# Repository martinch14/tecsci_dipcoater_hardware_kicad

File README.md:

Diseño de Circuitos Integrados de la Carrera de Especialización en Sistemas Embebidos UBA

El siguiente diseño incluye el circuito integrado TMC5130 de la empresa TRINAMIC para el manejo de motores paso a paso
conectado con el módulo del microcontrolador ESP32D

Martin Abel Gambarotta
8vo Cohorte

Vista 3D:

Real: Fabricada y montada en Argentina Ernesto Mayer S.A. +  Asembli S.A.

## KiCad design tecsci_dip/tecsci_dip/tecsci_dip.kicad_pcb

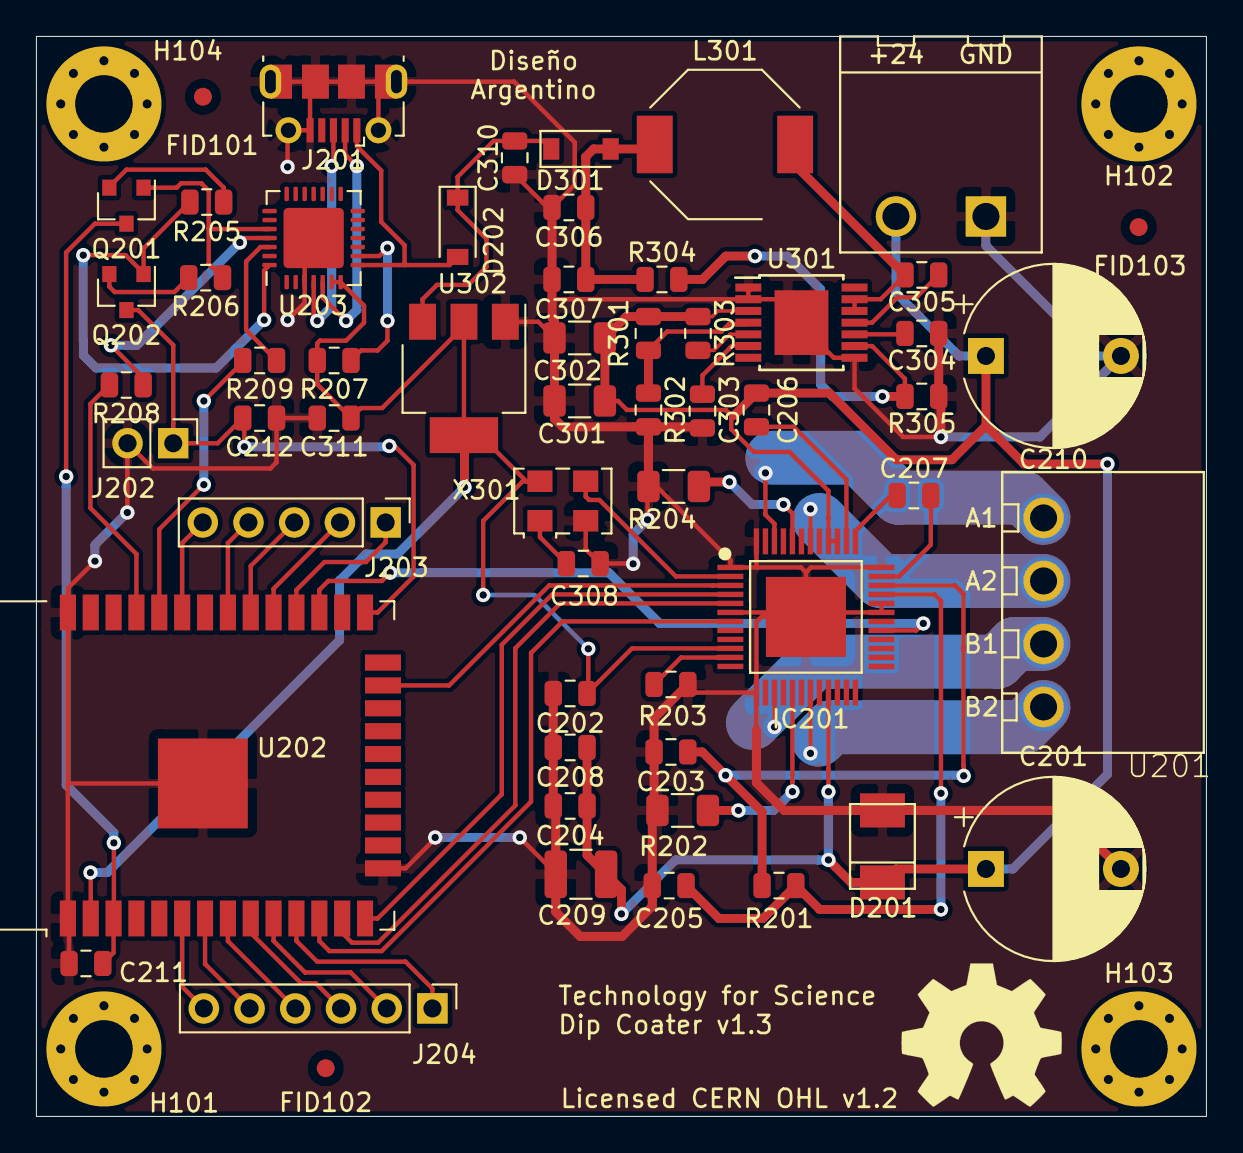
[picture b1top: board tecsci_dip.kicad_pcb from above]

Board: 2 copper layers, 65.0 x 60.0 mm, 62 parts (0 on the bottom side), 56 nets.

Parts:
C201, C210: 150uF/63V; CP_Radial_D10.0mm_P7.50mm
C202, C204, C206, C208: 100nF/50V; C_0805_2012Metric
C203: 470nF/16V; C_0805_2012Metric
C205: 4.7uF/16V; C_0805_2012Metric
C207, C303: 22nF/50V; C_0805_2012Metric
C209: 4.7uF/100V; C_1210_3225Metric
C211, C212: 0.1uF/10V; C_0805_2012Metric
C301: 2.2uF/100V; C_1206_3216Metric
C302: 100nF/100V; C_1206_3216Metric
C304: 1uF/50V; C_0805_2012Metric
C305: 10nF/10V; C_0805_2012Metric
C306, C307, C311: 10uF/10V; C_0805_2012Metric
C308: 10nF/16V; C_0805_2012Metric
C310: 100nF/10V; C_0805_2012Metric
D201: SMBJ43A; SMB
D202, D301: PMEG3020CEH; D_SOD-123
FID101, FID102, FID103: Fiducial; Fiducial_1mm_Mask2mm
H101, H102, H103, H104: MountingHole; MountingHole_3.2mm_M3_Pad_Via
IC201: TMC5130; QFP50P900X900X113-49N_NOFID
J201: USB_B_Micro; USB_Micro-B_Molex-105017-0001
J202: Boot; PinHeader_1x02_P2.54mm_Vertical
J203: Conn_01x05; PinHeader_1x05_P2.54mm_Vertical
J204: Conn_01x06; PinHeader_1x06_P2.54mm_Vertical
L301: SRU8043; L_Bourns-SRU8043
OSHWA101: Logo_Open_Hardware_Small; OSHW-Symbol_8.9x8mm_SilkScreen
POWER_IN301: POL_HEADER; AKL349_02_POL
Q201, Q202: S8050; SOT-23
R201: 2R2/1%; R_0805_2012Metric
R202, R204: 0R15/1%; R_1206_3216Metric
R203: 0R/1%; R_0805_2012Metric
R205, R206: 10K/1%; R_0805_2012Metric
R207: 4.7K/1%; R_0805_2012Metric
R208, R209: 1K/1%; R_0805_2012Metric
R301: 30k/1%; R_0805_2012Metric
R302: 6.8k/1%; R_0805_2012Metric
R303: 150k/1%; R_0805_2012Metric
R304: 3.3k/1%; R_0805_2012Metric
R305: 2.2k/1%; R_0805_2012Metric
U201: AKL182_04_POL_HEADER; AKL169_04_POL
U202: ESP32-WROOM-32D; ESP32-WROOM-32
U203: CP2102N-A01-GQFN28; QFN-28-1EP_5x5mm_P0.5mm_EP3.35x3.35mm
U301: Regulador_LM5161; TSSOP-14-1EP_4.4x5mm_P0.65mm
U302: LD1117S33TR_SOT223; SOT-223-3_TabPin2
X301: Oscillator_636L3C016M00000; Oscillator_SMD_EuroQuartz_XO53-4Pin_5.0x3.2mm

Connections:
+3V3: C202.1, C311.1, IC201.10, R207.2, U202.2, U203.6, U203.7, U302.2, X301.4
+5V: C306.1, C307.1, D301.2, L301.2, R304.1
+5VD: C310.1, D202.1, D301.1, U302.3
+24V: C201.1, C204.1, C206.1, C208.1, C209.1, C210.1, C301.1, C302.1, D201.C, IC201.21, IC201.39, IC201.40, POWER_IN301.2, R301.2, R303.2, U301.3
/alimentacion/CLK16: IC201.2, X301.3
/esp32_tmc5130_/CSN: IC201.3, U202.23
/esp32_tmc5130_/D+: J201.3, U203.4
/esp32_tmc5130_/D-: J201.2, U203.5
/esp32_tmc5130_/DRV_ENA: IC201.29, U202.27
/esp32_tmc5130_/DTR: Q202.1, R205.2, U203.28
/esp32_tmc5130_/EN: C211.1, Q201.3, U202.3
/esp32_tmc5130_/IO0: C212.1, J202.1, Q202.3, U202.25
/esp32_tmc5130_/IO29: J203.2, U202.29
/esp32_tmc5130_/MISO: IC201.7, U202.12
/esp32_tmc5130_/MOSI: IC201.5, U202.13
/esp32_tmc5130_/RTS: Q201.1, R206.2, U203.24
/esp32_tmc5130_/RX: R209.1, U202.34
/esp32_tmc5130_/SCK: IC201.4, U202.14
/esp32_tmc5130_/TX: R208.1, U202.35
/esp32_tmc5130_/VBUS: D202.2, J201.1, U203.8
GND: C201.2, C202.2, C203.2, C204.2, C205.1, C208.2, C209.2, C210.2, C211.2, C212.2, C301.2, C302.2, C303.2, C304.2, C306.2, C307.2, C308.2, C310.2, C311.2, D201.A, IC201.1, IC201.6, IC201.13, IC201.31, IC201.32, IC201.36, IC201.48, IC201.PAD, J201.5, J201.6, J202.2, POWER_IN301.1, R202.2, R203.2, R204.2, R302.1, R305.2, U202.1, U202.15, U202.38, U203.3, U203.29, U301.1, U301.2, U301.8, U301.15, U302.1, X301.2
unnamed: C203.1, IC201.34, R201.2
unnamed: C205.2, IC201.33, R201.1
unnamed: C206.2, IC201.38
unnamed: C207.1, IC201.35
unnamed: C207.2, IC201.37
unnamed: C303.1, U301.6
unnamed: C304.1, U301.10
unnamed: C305.1, L301.1, U301.12, U301.13
unnamed: C305.2, U301.11
unnamed: C308.1, X301.1
unnamed: IC201.11, R203.1
unnamed: IC201.15, U201.2
unnamed: IC201.17, R202.1
unnamed: IC201.19, U201.1
unnamed: IC201.42, U201.3
unnamed: IC201.44, R204.1
unnamed: IC201.46, U201.4
unnamed: J203.1, U202.28
unnamed: J203.3, U202.30
unnamed: J203.4, U202.31
unnamed: J203.5, U202.33
unnamed: J204.1, U202.11
unnamed: J204.2, U202.10
unnamed: J204.3, U202.9
unnamed: J204.4, U202.8
unnamed: J204.5, U202.7
unnamed: J204.6, U202.6
unnamed: Q201.2, R205.1
unnamed: Q202.2, R206.1
unnamed: R207.1, U203.9
unnamed: R208.2, U203.25
unnamed: R209.2, U203.26
unnamed: R301.1, R302.2, U301.4
unnamed: R303.1, U301.5
unnamed: R304.2, R305.1, U301.9

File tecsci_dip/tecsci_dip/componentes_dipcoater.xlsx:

Qty | Reference(s) | Value | Footprint | digikey# | manf | manf#
2 | C201, C210 | 150uF/63V | Capacitor_THT:CP_Radial_D10.0mm_P7.50mm | P15406-ND | Panasonic Electronic Components | EEU-FR1J151
4 | C202, C204, C206, C208 | 100nF/50V | Capacitor_SMD:C_0805_2012Metric
1 | C203 | 470nF/16V | Capacitor_SMD:C_0805_2012Metric
1 | C205 | 4.7uF/16V | Capacitor_SMD:C_0805_2012Metric
2 | C207, C303 | 22nF/50V | Capacitor_SMD:C_0805_2012Metric
1 | C209 | 4.7uF/100V | Capacitor_SMD:C_1210_3225Metric
2 | C211, C212 | 0.1uF/10V | Capacitor_SMD:C_0805_2012Metric
1 | C301 | 2.2uF/100V | Capacitor_SMD:C_1206_3216Metric
1 | C302 | 100nF/100V | Capacitor_SMD:C_1206_3216Metric
1 | C304 | 1uF/50V | Capacitor_SMD:C_0805_2012Metric
1 | C305 | 10nF/10V | Capacitor_SMD:C_0805_2012Metric
3 | C306, C307, C311 | 10uF/10V | Capacitor_SMD:C_0805_2012Metric
1 | C308 | 10nF/16V | Capacitor_SMD:C_0805_2012Metric
1 | C310 | 100nF/10V | Capacitor_SMD:C_0805_2012Metric
1 | D201 | SMBJ43A | TMC5130-Eval_v15:SMB | SMBJ43AFSTR-ND | Taiwan Semiconductor Corporation | SMBJ43A
2 | D202, D301 | PMEG3020CEH | Diode_SMD:D_SOD-123 | 1727-3873-2-ND | Nexperia USA Inc. | PMEG3020EH,115
1 | IC201 | TMC5130 | TMC5130-Eval_v15:QFP50P900X900X113-49N_NOFID | 1460-1124-ND | Trinamic Motion Control GmbH | TMC5130A-TA
1 | J201 | USB_B_Micro | Connector_USB:USB_Micro-B_Molex-105017-0001 | WM1399CT-ND
1 | J202 | Boot | Connector_PinHeader_2.54mm:PinHeader_1x02_P2.54mm_Vertical | 5-146285-2-ND
1 | J203 | Conn_01x05 | Connector_PinHeader_2.54mm:PinHeader_1x05_P2.54mm_Vertical | SAM15242-ND
1 | J204 | Conn_01x06 | Connector_PinHeader_2.54mm:PinHeader_1x06_P2.54mm_Vertical | A121372-ND
1 | L301 | SRU8043 | Inductor_SMD:L_Bourns-SRU8043 | SRU8043-100YTR-ND | Bourns Inc. | SRU8043-100Y
1 | POWER_IN301 | POL_HEADER | TMC5130-Eval_v15:AKL349_02_POL | 277-1106-ND
2 | Q201, Q202 | S8050 | Package_TO_SOT_SMD:SOT-23 | MMSS8050-H-TPMSCT-ND
1 | R201 | 2R2/1% | Resistor_SMD:R_0805_2012Metric
2 | R202, R204 | 0R15/1% | Resistor_SMD:R_1206_3216Metric
1 | R203 | 0R/1% | Resistor_SMD:R_0805_2012Metric
2 | R205, R206 | 10K/1% | Resistor_SMD:R_0805_2012Metric
1 | R207 | 4.7K/1% | Resistor_SMD:R_0805_2012Metric
2 | R208, R209 | 1K/1% | Resistor_SMD:R_0805_2012Metric
1 | R301 | 30k/1% | Resistor_SMD:R_0805_2012Metric
1 | R302 | 6.8k/1% | Resistor_SMD:R_0805_2012Metric
1 | R303 | 150k/1% | Resistor_SMD:R_0805_2012Metric
1 | R304 | 3.3k/1% | Resistor_SMD:R_0805_2012Metric
1 | R305 | 2.2k/1% | Resistor_SMD:R_0805_2012Metric
1 | U201 | AKL182_04_POL_HEADER | TMC5130-Eval_v15:AKL169_04_POL | 277-1208-ND
1 | U202 | ESP32-WROOM-32D | RF_Module:ESP32-WROOM-32 | 1904-1023-2-ND
1 | U203 | CP2102N-A01-GQFN28 | Package_DFN_QFN:QFN-28-1EP_5x5mm_P0.5mm_EP3.35x3.35mm | 336-5890-1-ND
1 | U301 | Regulador_LM5161 | Package_SO:TSSOP-14-1EP_4.4x5mm_P0.65mm | 296-47791-2-ND | Texas Instruments | LM5161QPWPRQ1
1 | U302 | LD1117S33TR_SOT223 | Package_TO_SOT_SMD:SOT-223-3_TabPin2 | 497-1242-1-ND
1 | X301 | Oscillator_636L3C016M00000 | Oscillator:Oscillator_SMD_EuroQuartz_XO53-4Pin_5.0x3.2mm | CTX691CT-ND

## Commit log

2020-01-22 version 1.3
2020-01-24 version fabricada
2020-06-23 agrego imagen placa fabricada
2020-06-23 cambio pixel
2020-06-23 resize image

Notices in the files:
tecsci_dip/tecsci_dip/tecsci_dip.kicad_pcb:
Tecsci  Tecnología para Ciencia Licensed under CERN OHL v.1.2
Licensed CERN OHL v1.2
